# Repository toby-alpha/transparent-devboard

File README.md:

# ESP32-C3 Based (not so) Transparent Dev Board

* unforchantly due to manufacturing constraints, the transparent board has to come to an end.. (it was 300USD for 20 transparents). I'll look for ways to produce it after this, and probably persue it as a personal endeavor.*

The Dev Board is based off the ESP32 C3 Mini module. It contains a USB-C port, power LED, user LED, 3x WS2812B 2020 Adressable LEDs, >6V voltage input, as well as all GPIO being broken out. The USB-C connector is inline to conform to a slim profile. It also has a JST SH connector for i2C connections.

It's specially manufactured from a transparent FR4 material to give it's unique look.

## Why I designed this?

I was really intrigued with the concept of a transparent PCB, after seeing a JLCPCB advertisement for it. This prompted me to create an ESP devboard, that would be useful in many scenarios, while also exploring this new technology. The PCB also serves as a great method of education, showing inside of the complex electronics.

## BOM

|Item                     |Cost (AUD)|Cost (USD)|Source    |Link                                                 |
|-------------------------|----------|----------|----------|-----------------------------------------------------|
|Components Parts         |45        |29        |LCSC      |PDF Quote Upon Request                               |
|Hot Plate                |34        |22        |Aliexpress|[https://www.aliexpress.com/item/1005008125355441.html](https://www.aliexpress.com/item/1005007010531329.html)|
|Misc (Solder Paste.. Etc)|30        |19.5      |Aliexpress|                                                     |
|PCB + Stencil    |15        |9.75      |JLCPCB    |                                                     |
|                         |          |          |          |                                                     |
|                         |Total     |81   |          |                                                     |

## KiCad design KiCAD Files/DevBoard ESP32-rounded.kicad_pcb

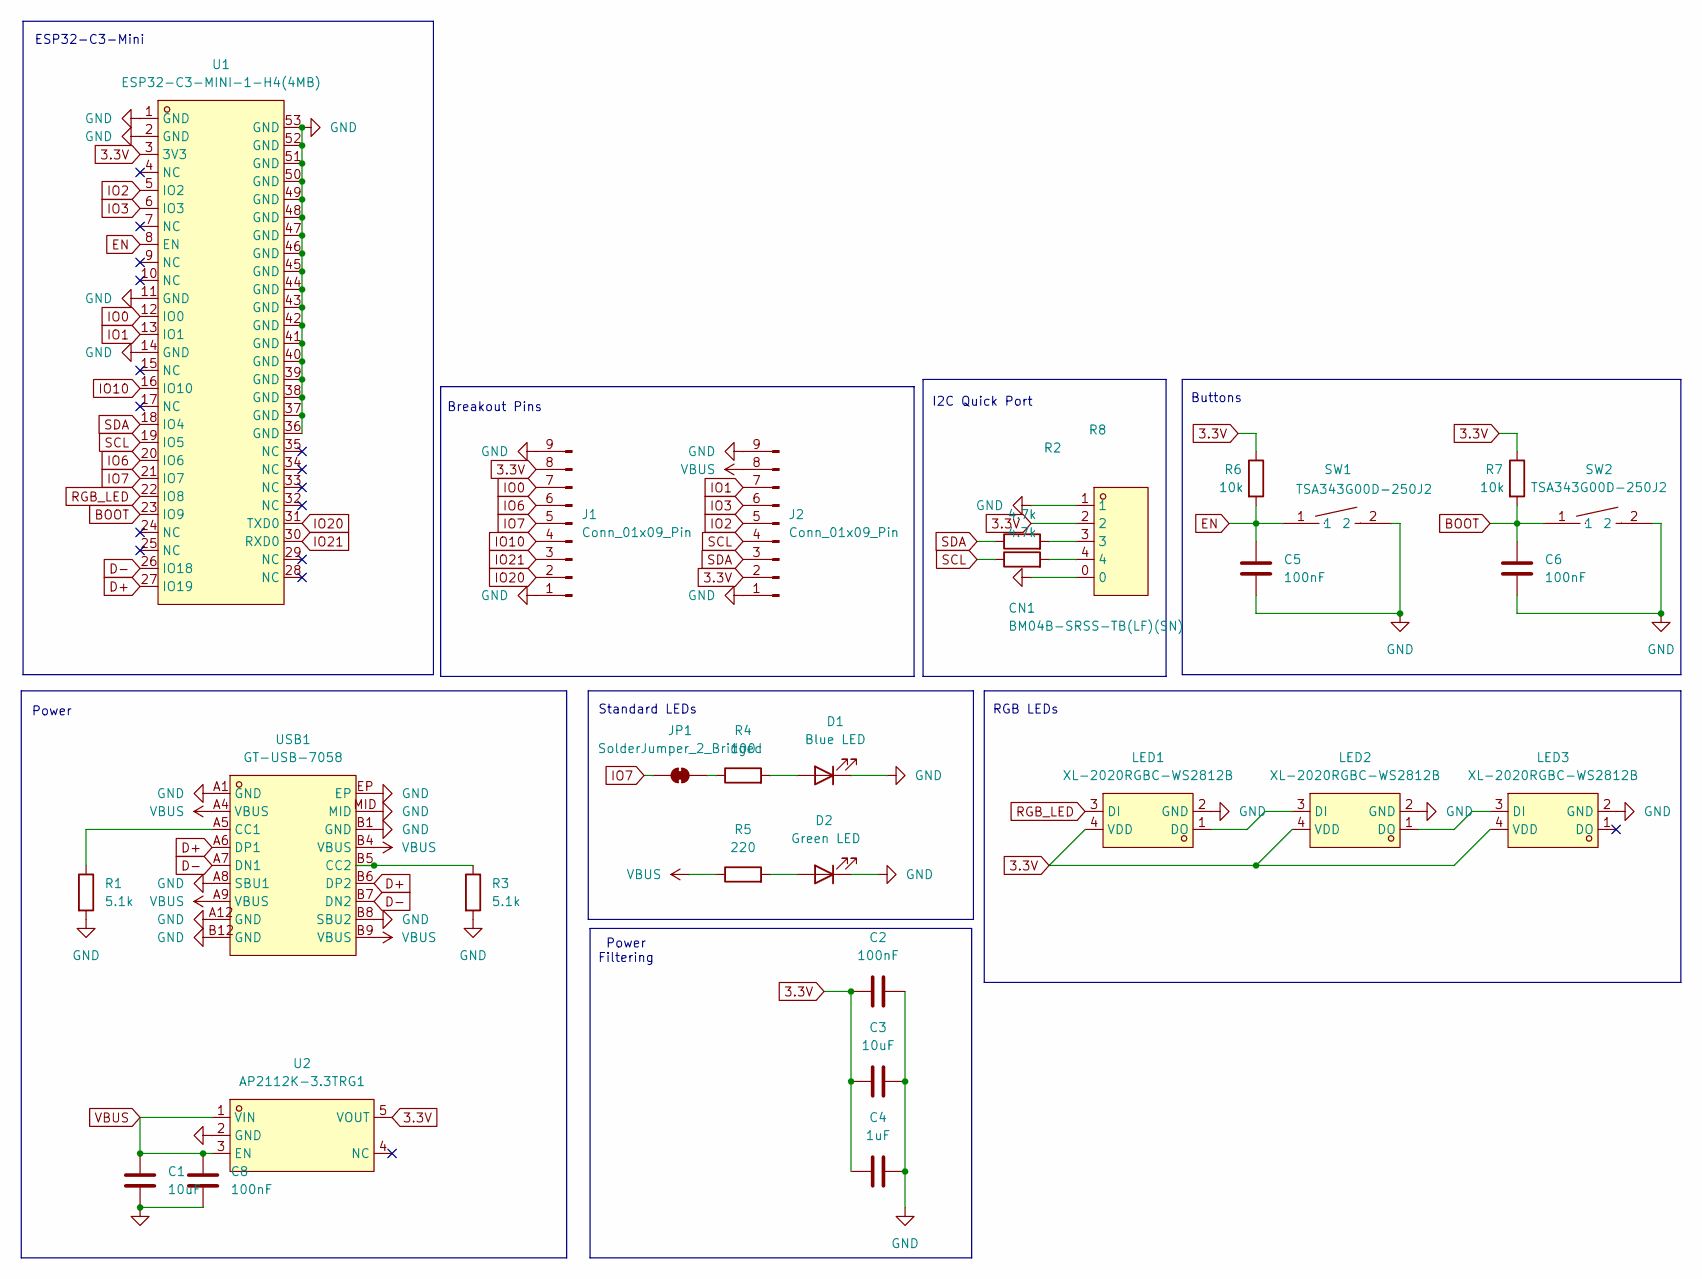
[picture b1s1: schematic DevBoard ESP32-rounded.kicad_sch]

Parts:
C1, C3: 10uF; C_0805_2012Metric
C2, C5, C6, C8: 100nF; C_0603_1608Metric
C4: 1uF; C_0603_1608Metric
CN1: BM04B-SRSS-TB(LF)(SN); CONN-SMD_BM04B-SRSS-TB; LCSC Part C160390
D1: Blue LED; LED_0805_2012Metric
D2: Green LED; LED_0805_2012Metric
J1, J2: Conn_01x09_Pin; PinSocket_1x09_P2.54mm_Vertical
JP1: SolderJumper_2_Bridged; SolderJumper-2_P1.3mm_Bridged_RoundedPad1.0x1.5mm
LED1, LED2, LED3: XL-2020RGBC-WS2812B; LED-SMD_4P-L2.0-W2.0-BR-1; LCSC Part C5349955
R1, R3: 5.1k; R_0603_1608Metric
R2, R8: 4.7k; R_0603_1608Metric
R4: 100; R_0603_1608Metric
R5: 220; R_0603_1608Metric
R6, R7: 10k; R_0603_1608Metric
SW1, SW2: TSA343G00D-250J2; SW-SMD_L4.0-W2.9-P4.15-EH; LCSC Part C354947
U1: ESP32-C3-MINI-1-H4(4MB); WIFIM-SMD_ESP32-C3-MINI-1; LCSC Part C2934569
U2: AP2112K-3.3TRG1; SOT-25-5_L2.9-W1.6-P0.95-LS2.8-BL; LCSC Part C51118
USB1: GT-USB-7058; USB-C-SMD_GT-USB-7058; LCSC Part C2762991

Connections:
3.3V: C2.1, C3.2, C4.2, CN1.2, J1.8, J2.2, LED1.4 (VDD), LED2.4 (VDD), LED3.4 (VDD), R6.1, R7.1, U1.3 (3V3), U2.5 (VOUT)
BOOT: C6.1, R7.2, SW2.1, U1.23 (IO9)
D+: U1.27 (IO19), USB1.A6 (DP1), USB1.B6 (DP2)
D-: U1.26 (IO18), USB1.A7 (DN1), USB1.B7 (DN2)
EN: C5.1, R6.2, SW1.1, U1.8 (EN)
GND: C1.2, C2.2, C3.1, C4.1, C5.2, C6.2, C8.2, CN1.0, CN1.1, D1.1 (K), D2.1 (K), J1.1, J1.9, J2.1, J2.9, LED1.2 (GND), LED2.2 (GND), LED3.2 (GND), R1.2, R3.2, SW1.2, SW2.2, U1.1 (GND), U1.2 (GND), U1.11 (GND), U1.14 (GND), U1.36 (GND), U1.37 (GND), U1.38 (GND), U1.39 (GND), U1.40 (GND), U1.41 (GND), U1.42 (GND), U1.43 (GND), U1.44 (GND), U1.45 (GND), U1.46 (GND), U1.47 (GND), U1.48 (GND), U1.49 (GND), U1.50 (GND), U1.51 (GND), U1.52 (GND), U1.53 (GND), U2.2 (GND), USB1.A1 (GND), USB1.A8 (SBU1), USB1.A12 (GND), USB1.B1 (GND), USB1.B8 (SBU2), USB1.B12 (GND), USB1.EP, USB1.MID
IO0: J1.7, U1.12 (IO0)
IO1: J2.7, U1.13 (IO1)
IO2: J2.5, U1.5 (IO2)
IO3: J2.6, U1.6 (IO3)
IO6: J1.6, U1.20 (IO6)
IO7: J1.5, JP1.1 (A), U1.21 (IO7)
IO10: J1.4, U1.16 (IO10)
IO20: J1.2, U1.31 (TXD0)
IO21: J1.3, U1.30 (RXD0)
unnamed: CN1.3, R2.2
unnamed: CN1.4, R8.2
unnamed: D1.2 (A), R4.2
unnamed: D2.2 (A), R5.2
unnamed: JP1.2 (B), R4.1
unnamed: LED1.1 (DO), LED2.3 (DI)
unnamed: LED2.1 (DO), LED3.3 (DI)
unnamed: R1.1, USB1.A5 (CC1)
unnamed: R3.1, USB1.B5 (CC2)
RGB_LED: LED1.3 (DI), U1.22 (IO8)
SCL: J2.4, R8.1, U1.19 (IO5)
SDA: J2.3, R2.1, U1.18 (IO4)
VBUS: C1.1, C8.1, J2.8, R5.1, U2.1 (VIN), U2.3 (EN), USB1.A4 (VBUS), USB1.A9 (VBUS), USB1.B4 (VBUS), USB1.B9 (VBUS)

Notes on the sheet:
Buttons
I2C Quick Port
RGB LEDs
ESP32-C3-Mini
Breakout Pins
Power Filtering
Standard LEDs
Power

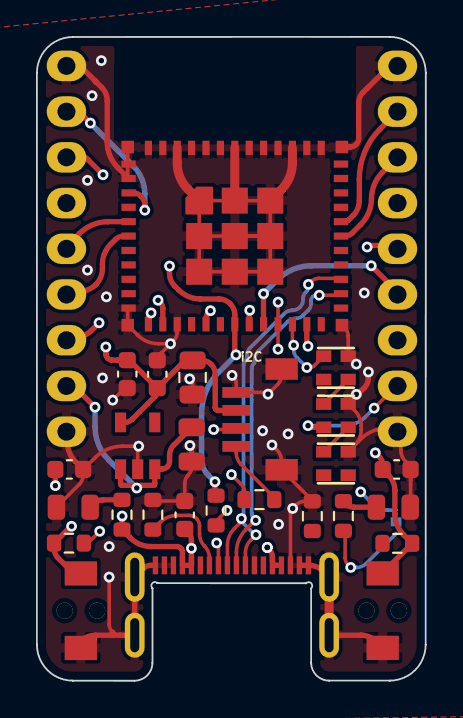
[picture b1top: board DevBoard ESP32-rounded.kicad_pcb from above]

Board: 4 copper layers, 21.6 x 35.8 mm, 29 parts (1 on the bottom side), 28 nets.

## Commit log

2025-07-07 Rename Production 2.zip to Production NOT TRANSPARENT.zip
2025-07-08 added new folder
